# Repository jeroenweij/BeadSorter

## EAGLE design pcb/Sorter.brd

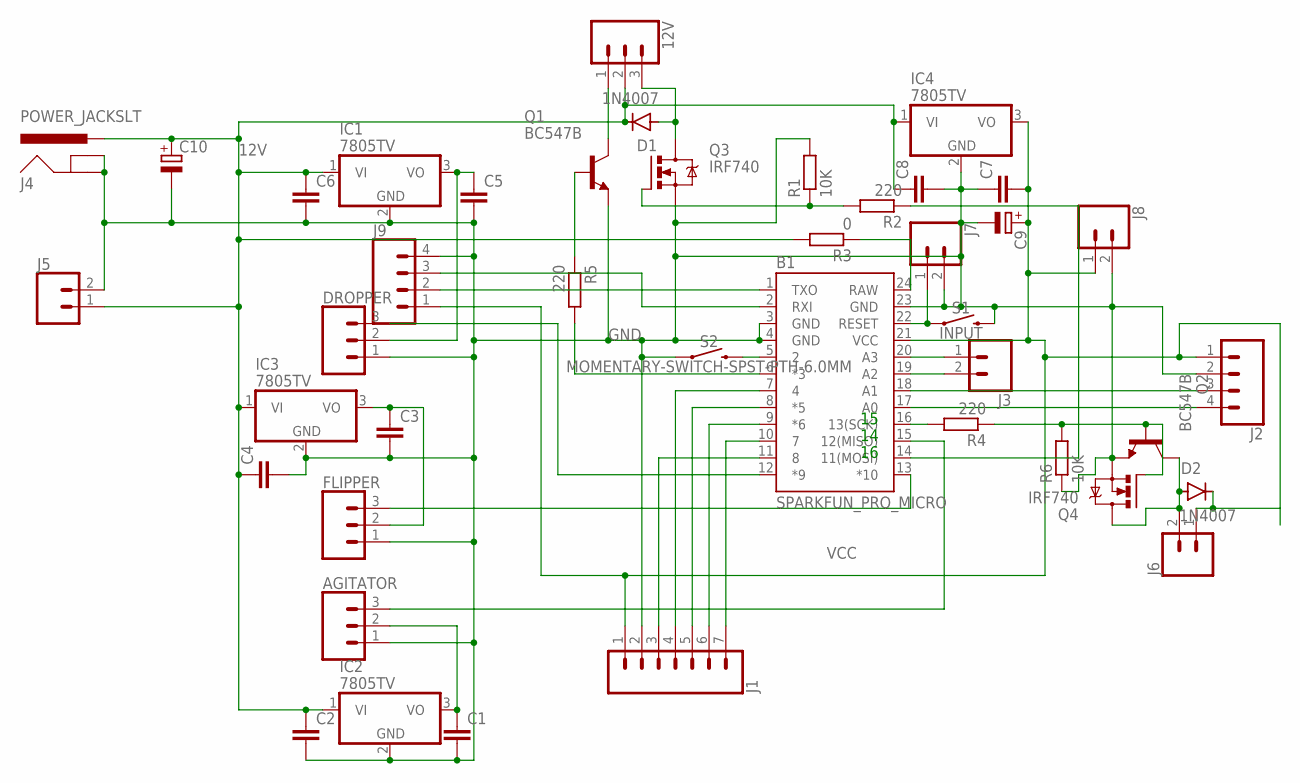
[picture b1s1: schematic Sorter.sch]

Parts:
12V: CONN_03LONGPADS; 1X03_LONGPADS
AGITATOR: CONN_03LONGPADS; 1X03_LONGPADS
B1: SPARKFUN_PRO_MICRO
C1, C2, C3, C4, C5, C6, C7, C8: C2.5/2; C2.5-2
C9, C10: CPOL-EUE2.5-5; E2,5-5
D1, D2: 1N4007; DO-41
DROPPER: CONN_03LONGPADS; 1X03_LONGPADS
FLIPPER: CONN_03LONGPADS; 1X03_LONGPADS
IC1, IC2, IC3, IC4: 7805TV; TO220V
J1: CONN_07LONGPADS; 1X07_LONGPADS
J2: CONN_04LONGPADS; 1X04_LONGPADS
J3, J8: CONN_02; 1X02
J4: POWER_JACKSLT; POWER_JACK_SLOT
J5: CONN_023.5MM; SCREWTERMINAL-3.5MM-2
J6, J7: CONN_02PTH3; 1X02_LONGPADS
J9: CONN_04; 1X04
Q1, Q2: BC547B; TO92
Q3, Q4: IRF740; TO220BV
R1, R6: 10K; 0204/7
R2, R4, R5: 220; 0204/7
R3: 0; 0204/7
S1: INPUT; TACTILE_SWITCH_PTH_6.0MM
S2: MOMENTARY-SWITCH-SPST-PTH-6.0MM; TACTILE_SWITCH_PTH_6.0MM

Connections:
12V: 12V.2, C2.1, C4.1, C6.1, C8.1, C10.+, D1.C, IC1.1 (VI), IC2.1 (VI), IC3.1 (VI), IC4.1 (VI), J4.PWR, J5.1, R3.2
GND: AGITATOR.1, B1.3 (GND), B1.4 (GND), B1.23 (GND), C1.2, C2.2, C3.2, C4.2, C5.2, C6.2, C7.1, C8.2, C9.-, C10.-, DROPPER.1, FLIPPER.1, IC1.2 (GND), IC2.2 (GND), IC3.2 (GND), IC4.2 (GND), J1.2, J2.2, J4.GND@1 (GNDBREAK), J4.GND@2 (GND), J5.2, J7.2, J8.2, J9.4, Q1.1 (E), Q2.1 (E), Q3.S, Q4.S, R1.2, R6.1, S1.3 (2), S2.1
unnamed: AGITATOR.2, C1.1, IC2.3 (VO)
unnamed: C5.1, DROPPER.2, IC1.3 (VO)
unnamed: C3.1, FLIPPER.2, IC3.3 (VO)
unnamed: B1.12 (*9), DROPPER.3
unnamed: B1.13 (*10), FLIPPER.3
unnamed: AGITATOR.3, B1.15 (12(MISO))
unnamed: 12V.1, Q1.3 (C)
unnamed: B1.6 (*3), R5.2
unnamed: B1.14 (11(MOSI)), R2.1
unnamed: 12V.3, D1.A, Q3.D
unnamed: Q3.G, R1.1, R2.2
unnamed: B1.10 (7), J1.7
unnamed: B1.9 (*6), J1.6
unnamed: B1.8 (*5), J1.5
unnamed: B1.7 (4), J1.4
unnamed: B1.11 (8), J1.3
unnamed: B1.2 (RXI), J9.3
unnamed: B1.24 (RAW), R3.1
unnamed: B1.19 (A2), J3.2
unnamed: B1.22 (RESET), J7.1, S1.1
unnamed: B1.5 (2), S2.3 (2)
unnamed: B1.1 (TXO), J9.2
unnamed: B1.18 (A1), J2.3
unnamed: B1.17 (A0), J2.4
unnamed: B1.16 (13(SCK)), R4.2
unnamed: Q2.2 (B), Q4.G, R4.1, R6.2
unnamed: Q1.2 (B), R5.1
unnamed: D2.A, J6.2, Q2.3 (C), Q4.D
unnamed: B1.20 (A3), J3.1
VCC: B1.21 (VCC), C7.2, C9.+, D2.C, IC4.3 (VO), J1.1, J2.1, J6.1, J8.1, J9.1

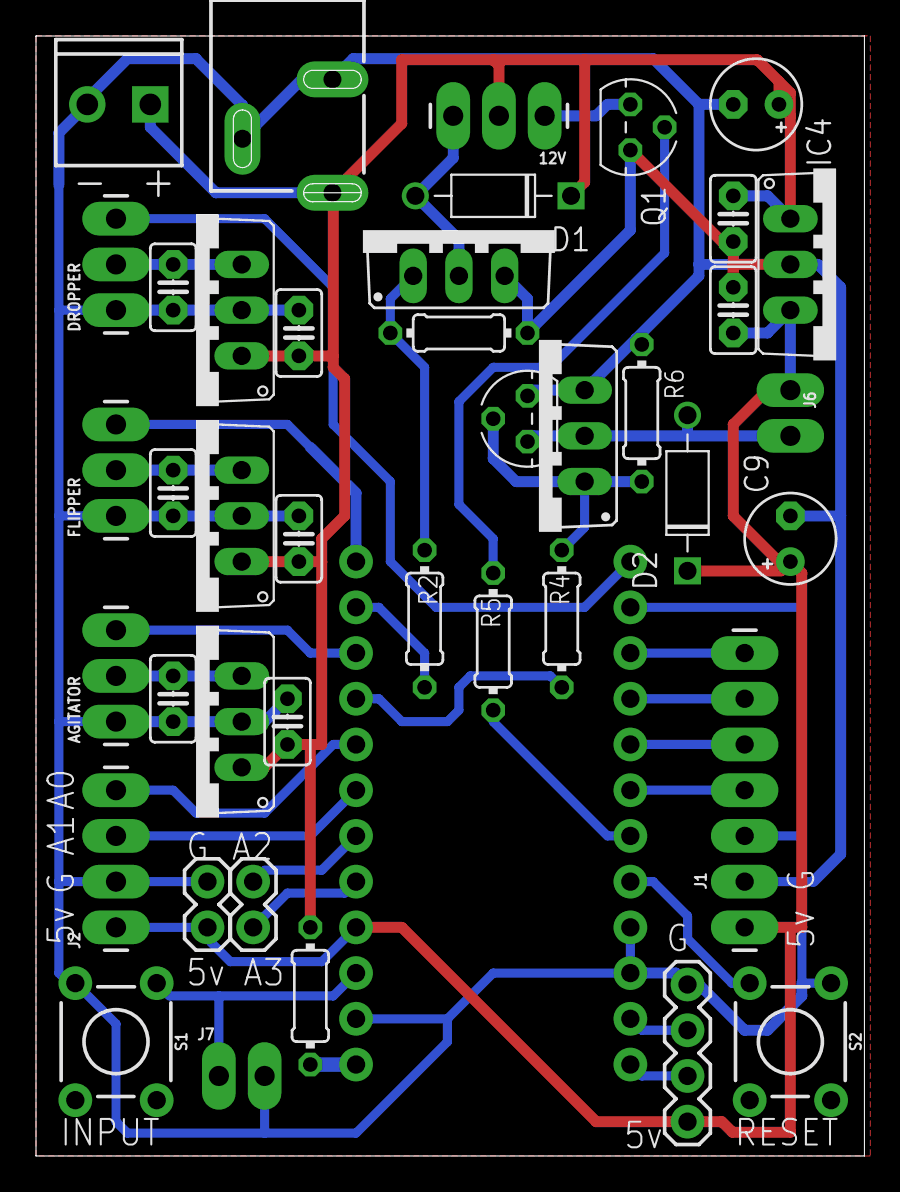
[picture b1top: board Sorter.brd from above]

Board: 2 copper layers, 46.0 x 62.2 mm, 42 parts (0 on the bottom side), 32 nets.

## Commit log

2020-12-29 Initial TCS sensor code
2020-12-29 Cleanup gitignore
2020-12-29 add ssprintf
2020-12-30 Add dropper an color
2020-12-31 Add adgitator
2021-01-01 Changes to code
2021-01-05 Add hardware pcb design
2021-01-06 Add pin header generation
2021-01-06 Move sketch to its own directory
2021-01-06 Add simulator for development
2021-01-06 use new pins.h for pin definitions
2021-01-06 Add mock system for functions that return something in simulation mode
2021-01-07 Add more colors
2021-01-07 Move ssprintf to its own header, and cleanup
2021-01-08 Add GUI to simulator
2021-01-08 Work on GUI add option to print text
2021-01-10 Improve color detection and add circle draw
2021-01-10 change server adressing to standard degrees
    and print dropper in gui
2021-12-04 work on color detection

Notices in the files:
parts and their libraries:
SparkFun-Connectors: Licensing: Creative Commons ShareAlike 4.0 International - https://creativecommons.org/licenses/by-sa/4.0
